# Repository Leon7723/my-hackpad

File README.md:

# my-hackpad
im making a macropad/hackpad for a stardance mission so i can learn kicad, hardware and a lot more of things to start making my own proyects

the firmware is still under work and im gonna drop it here as soon has i have it done, cuz i didnt have much time since school and now im doing my best to finish it, hope yall understand, even the reviewer :)

as soon as i finish all than i need for this im gonna drop them here so keep an eye on this repo

and the case for the hackpad is finished, thanks to a-fun-gi for helping making the case, you did an amazing work and thanks for contributing in this proyect

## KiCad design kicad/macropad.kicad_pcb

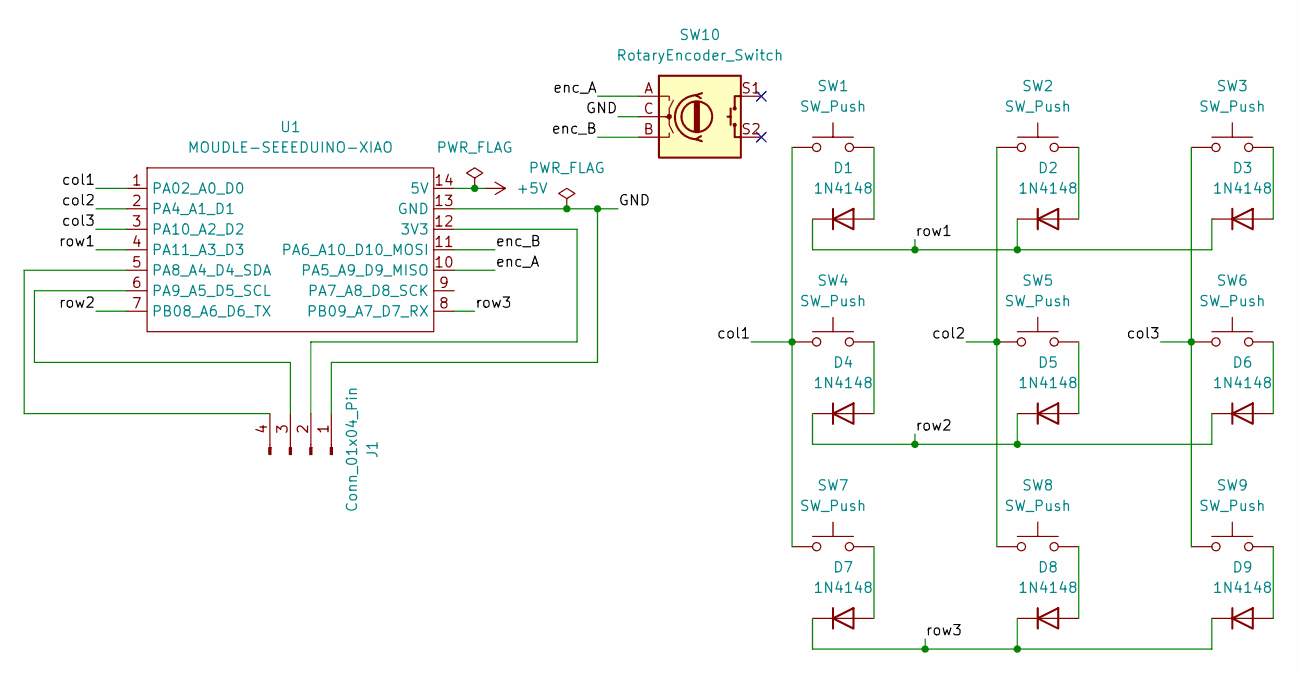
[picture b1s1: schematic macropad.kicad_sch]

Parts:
D1, D2, D3, D4, D5, D6, D7, D8, D9: 1N4148; D_DO-35_SOD27_P7.62mm_Horizontal
J1: Conn_01x04_Pin; PinHeader_1x04_P2.54mm_Vertical
SW1, SW2, SW3, SW4, SW5, SW6, SW7, SW8, SW9: SW_Push; SW_Cherry_MX_1.00u_PCB
SW10: RotaryEncoder_Switch; RotaryEncoder_Alps_EC11E-Switch_Vertical_H20mm
U1: MOUDLE-SEEEDUINO-XIAO; XIAO-Generic-Hybrid-14P-2.54-21X17.8MM

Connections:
+5V: U1.14 (5V)
/GND: J1.1, SW10.C, U1.13 (GND)
/col1: SW1.1, SW4.1, SW7.1, U1.1 (PA02_A0_D0)
/col2: SW2.1, SW5.1, SW8.1, U1.2 (PA4_A1_D1)
/col3: SW3.1, SW6.1, SW9.1, U1.3 (PA10_A2_D2)
/enc_A: SW10.A, U1.10 (PA5_A9_D9_MISO)
/enc_B: SW10.B, U1.11 (PA6_A10_D10_MOSI)
/row1: D1.1 (K), D2.1 (K), D3.1 (K), U1.4 (PA11_A3_D3)
/row2: D4.1 (K), D5.1 (K), D6.1 (K), U1.7 (PB08_A6_D6_TX)
/row3: D7.1 (K), D8.1 (K), D9.1 (K), U1.8 (PB09_A7_D7_RX)
unnamed: D1.2 (A), SW1.2
unnamed: D2.2 (A), SW2.2
unnamed: D3.2 (A), SW3.2
unnamed: D4.2 (A), SW4.2
unnamed: D5.2 (A), SW5.2
unnamed: D6.2 (A), SW6.2
unnamed: D7.2 (A), SW7.2
unnamed: D8.2 (A), SW8.2
unnamed: D9.2 (A), SW9.2
unnamed: J1.2, U1.12 (3V3)
unnamed: J1.3, U1.6 (PA9_A5_D5_SCL)
unnamed: J1.4, U1.5 (PA8_A4_D4_SDA)

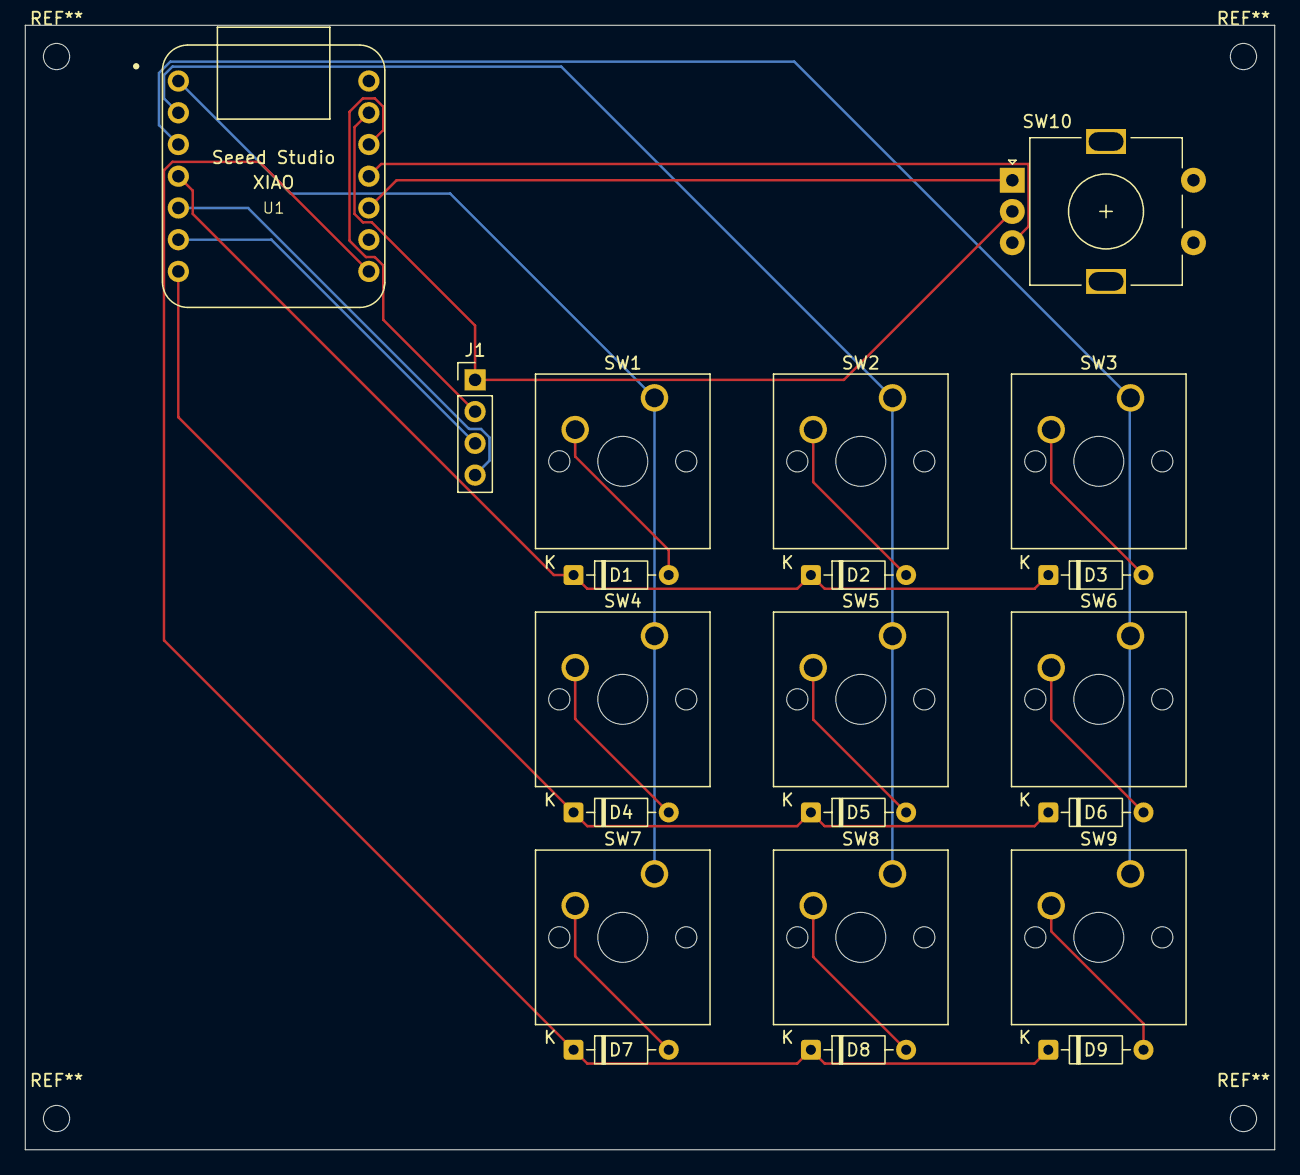
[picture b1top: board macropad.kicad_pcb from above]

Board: 2 copper layers, 100.0 x 90.0 mm, 21 parts (0 on the bottom side), 21 nets.
